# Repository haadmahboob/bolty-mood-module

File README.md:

# Bolty Mood Module

A 40 mm round, 2-layer PCB that gives the Bolty robot a face. An ATtiny85 drives two 3×2 "eyes" made of
12 reverse-mount SK6812MINI-E RGB LEDs, plus a buzzer and a pat button. The main robot sets the mood over
I2C at address `0x42`.

## Specs

| | |
|---|---|
| Board | 40 mm round, 2 layers, 1.6 mm FR-4 |
| MCU | ATtiny85-20SU (SOIC-8 wide), 8 MHz internal |
| LEDs | 12 × SK6812MINI-E, mounted on the back, shining through square holes |
| Sound | CMT-8504 magnetic buzzer, driven by an MMBT3904 |
| Input | 6 × 6 mm tactile button on the face |
| Connector | JST-PH 4-pin: GND, +5V, SCL, SDA |
| Programming | 2 × 3 ISP pads on the back |
| Interface | I2C slave `0x42`, write one byte: 0 idle, 1 happy, 2 sad, 3 angry, 4 sleepy, 5 surprised |

## Folders

| Path | Contents |
|---|---|
| `DESIGN.md` | Design notes: parts, pinout, LED layout |
| `BUILD.md` | Order → solder → program → test guide |
| `JOURNAL.md` | Build journal |
| `kicad/` | KiCad 10 project (schematic, PCB, custom symbol and footprint libraries) |
| `fab/` | Gerbers, drill files, BOM with buy links, positions, assembly PDFs, STEP model |
| `firmware/bolty_mood/` | ATtiny85 test firmware (ATTinyCore) |
| `tools/` | Python scripts that generated the schematic and board and ran the autorouter |
| `reel/` | Progress images and video |

## Status

- [x] Schematic (ERC clean)
- [x] PCB layout and routing (DRC: 0 errors, 0 unconnected, 0 schematic mismatches)
- [x] Fabrication files and BOM
- [ ] PCBs ordered
- [ ] Assembled and tested

## Credits

Designed with help from Claude Code (AI). See `JOURNAL.md` for who did what.

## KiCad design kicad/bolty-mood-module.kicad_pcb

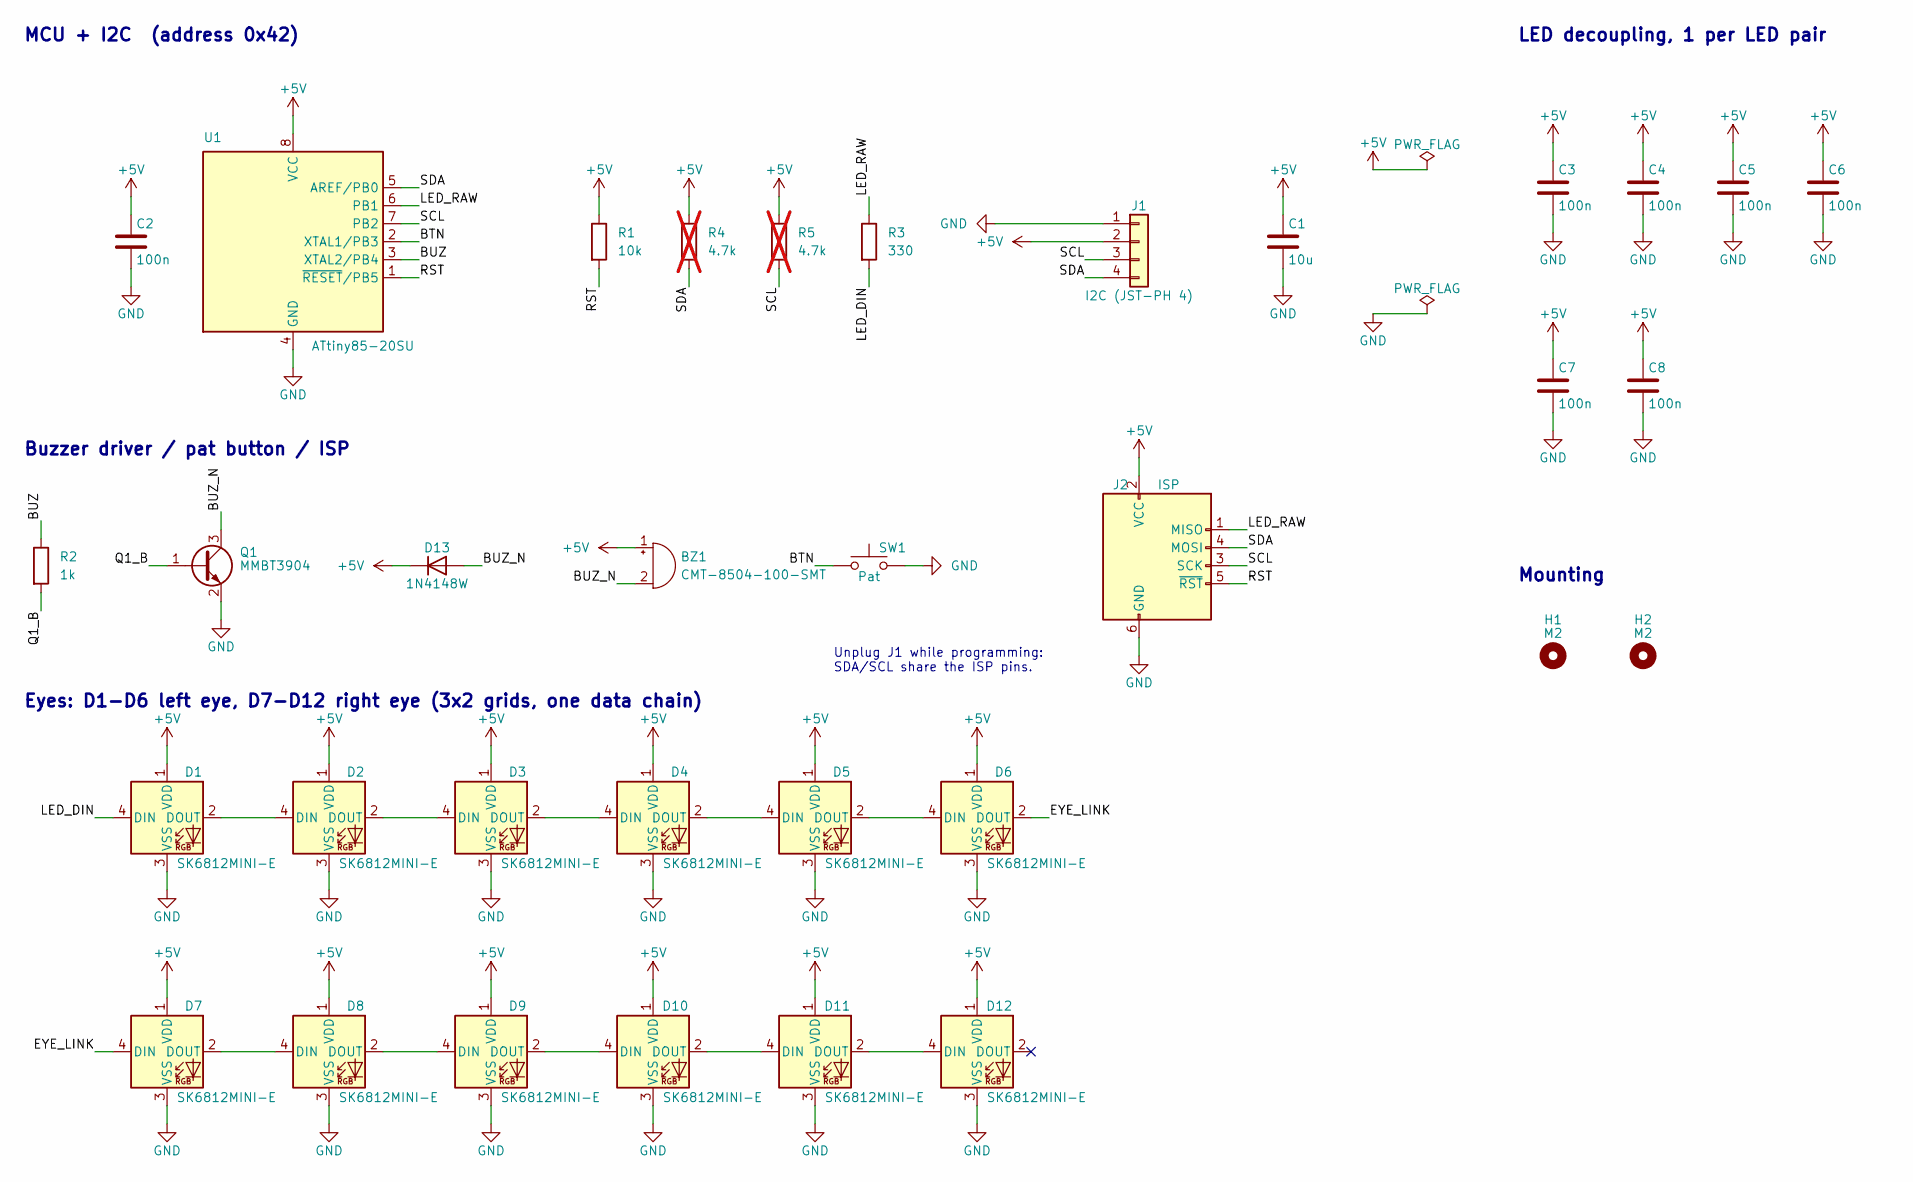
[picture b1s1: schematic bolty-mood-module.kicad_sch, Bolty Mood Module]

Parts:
BZ1: CMT-8504-100-SMT; MagneticBuzzer_CUI_CMT-8504-100-SMT; Part Number CMT-8504-100-SMT-TR
C1: 10u; C_0805_2012Metric; Part Number CL21A106KAYNNNE
C2, C3, C4, C5, C6, C7, C8: 100n; C_0603_1608Metric; Part Number CL10B104KB8NNNC
D1, D2, D3, D4, D5, D6, D7, D8, D9, D10, D11, D12: SK6812MINI-E; LED_SK6812MINI-E_3.2x2.8mm_P1.5mm_ReverseMount; Part Number 4960
D13: 1N4148W; D_SOD-123; Part Number 1N4148W-7-F
H1, H2: M2; MountingHole_2.2mm_M2
J1: I2C (JST-PH 4); JST_PH_B4B-PH-K_1x04_P2.00mm_Vertical; Part Number B4B-PH-K-S(LF)(SN)
J2: ISP; ISP_Pads_2x3_P2.54mm
Q1: MMBT3904; SOT-23; Part Number MMBT3904LT1G
R1: 10k; R_0603_1608Metric; Part Number RC0603FR-0710KL
R2: 1k; R_0603_1608Metric; Part Number RC0603FR-071KL
R3: 330; R_0603_1608Metric; Part Number RC0603FR-07330RL
R4, R5: 4.7k; R_0603_1608Metric; Part Number RC0603FR-074K7L; not fitted
SW1: Pat; SW_SPST_PTS645Sx43SMTR92; Part Number PTS645SM43SMTR92 LFS
U1: ATtiny85-20SU; SOIC-8_5.3x5.3mm_P1.27mm; Part Number ATTINY85-20SU

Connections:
+5V: BZ1.1 (+), C1.1, C2.1, C3.1, C4.1, C5.1, C6.1, C7.1, C8.1, D1.1 (VDD), D2.1 (VDD), D3.1 (VDD), D4.1 (VDD), D5.1 (VDD), D6.1 (VDD), D7.1 (VDD), D8.1 (VDD), D9.1 (VDD), D10.1 (VDD), D11.1 (VDD), D12.1 (VDD), D13.1 (K), J1.2, J2.2 (VCC), R1.1, R4.1, R5.1, U1.8 (VCC)
/BTN: SW1.1, U1.2 (XTAL1/PB3)
/BUZ: R2.1, U1.3 (XTAL2/PB4)
/BUZ_N: BZ1.2 (-), D13.2 (A), Q1.3 (C)
/EYE_LINK: D6.2 (DOUT), D7.4 (DIN)
/LED_DIN: D1.4 (DIN), R3.2
/LED_RAW: J2.1 (MISO), R3.1, U1.6 (PB1)
/Q1_B: Q1.1 (B), R2.2
/RST: J2.5 (~RST), R1.2, U1.1 (~RESET/PB5)
/SCL: J1.3, J2.3 (SCK), R5.2, U1.7 (PB2)
/SDA: J1.4, J2.4 (MOSI), R4.2, U1.5 (AREF/PB0)
GND: C1.2, C2.2, C3.2, C4.2, C5.2, C6.2, C7.2, C8.2, D1.3 (VSS), D2.3 (VSS), D3.3 (VSS), D4.3 (VSS), D5.3 (VSS), D6.3 (VSS), D7.3 (VSS), D8.3 (VSS), D9.3 (VSS), D10.3 (VSS), D11.3 (VSS), D12.3 (VSS), J1.1, J2.6 (GND), Q1.2 (E), SW1.2, U1.4 (GND)
unnamed: D1.2 (DOUT), D2.4 (DIN)
unnamed: D2.2 (DOUT), D3.4 (DIN)
unnamed: D3.2 (DOUT), D4.4 (DIN)
unnamed: D4.2 (DOUT), D5.4 (DIN)
unnamed: D5.2 (DOUT), D6.4 (DIN)
unnamed: D7.2 (DOUT), D8.4 (DIN)
unnamed: D8.2 (DOUT), D9.4 (DIN)
unnamed: D9.2 (DOUT), D10.4 (DIN)
unnamed: D10.2 (DOUT), D11.4 (DIN)
unnamed: D11.2 (DOUT), D12.4 (DIN)

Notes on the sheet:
MCU + I2C (address 0x42)
Buzzer driver / pat button / ISP
Unplug J1 while programming: SDA/SCL share the ISP pins.
Eyes: D1-D6 left eye, D7-D12 right eye (3x2 grids, one data chain)
LED decoupling, 1 per LED pair
Mounting

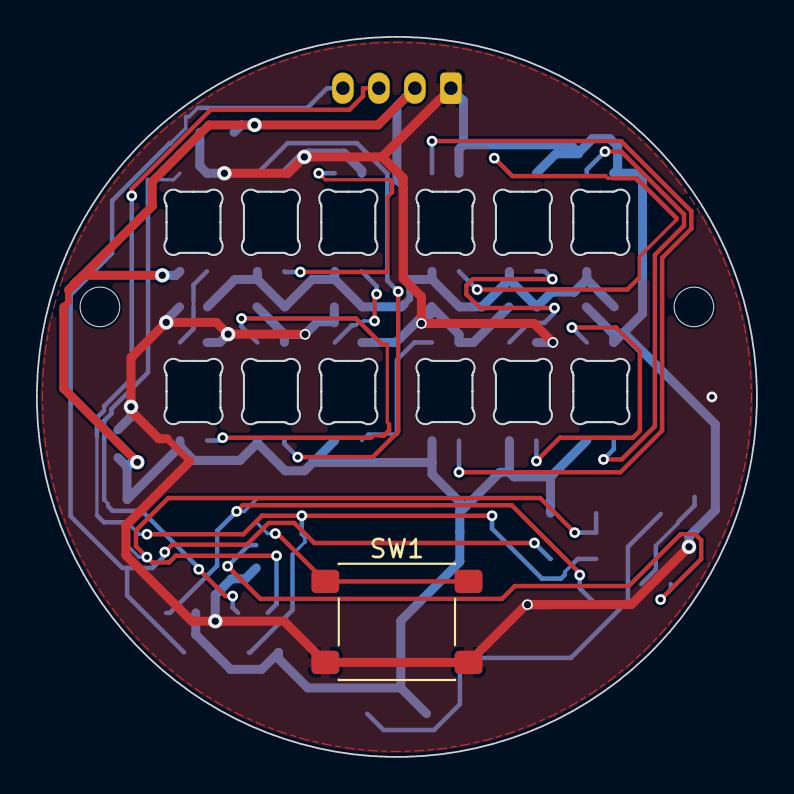
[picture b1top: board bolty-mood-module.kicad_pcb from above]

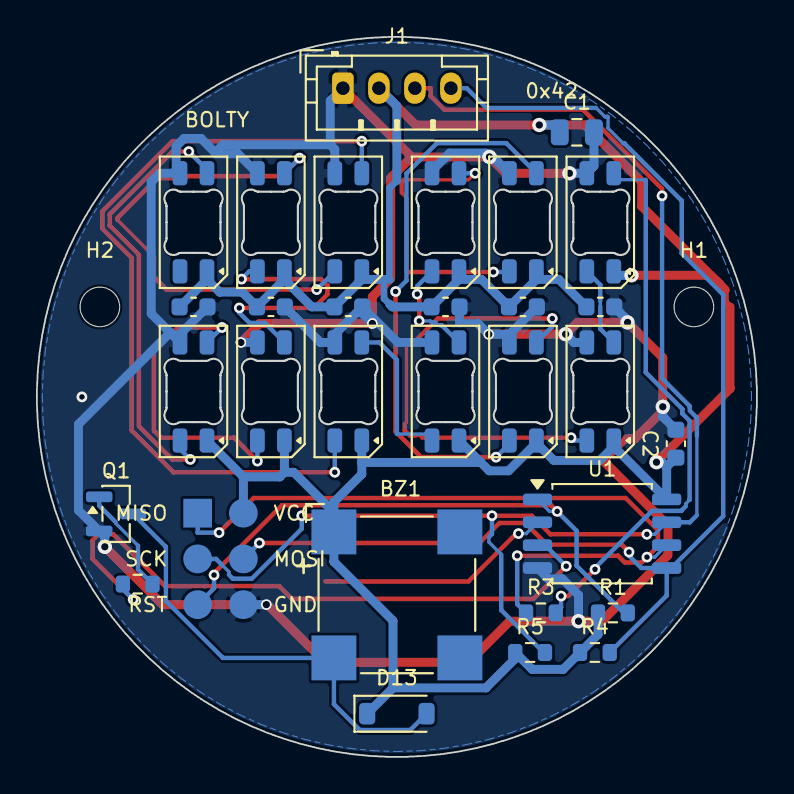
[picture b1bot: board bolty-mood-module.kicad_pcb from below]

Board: 2 copper layers, 40.0 x 40.0 mm, 34 parts (33 on the bottom side), 22 nets.

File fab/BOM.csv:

Reference,Qty per board,Value,Package / Footprint,Manufacturer,MPN,LCSC,Buy link,Notes
U1,1,ATtiny85-20SU,SOIC-8 (5.3 mm wide),Microchip,ATtiny85-20SU,,https://www.digikey.com/en/products/result?keywords=ATtiny85-20SU,Wide-body SOIC (208 mil) - not the narrow SN package
D1-D12,12,SK6812MINI-E,3.2x2.8 mm reverse-mount,Adafruit (OPSCO LEDs),4960,C5149201,https://www.digikey.com/en/products/detail/adafruit-industri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,10-pack of SK6812MINI-E (DigiKey 1528-4960-ND). Mounts on BACK and shines through the board hole
Q1,1,MMBT3904,SOT-23,onsemi,MMBT3904LT1G,,https://www.digikey.com/en/products/result?keywords=MMBT3904LT1G,
D13,1,1N4148W,SOD-123,Diodes Inc.,1N4148W-7-F,,https://www.digikey.com/en/products/result?keywords=1N4148W-7-F,Flyback diode across buzzer. Stripe = cathode = +5V side
BZ1,1,Magnetic buzzer 5 V,8.5x8.5 mm SMD,Same Sky (CUI),CMT-8504-100-SMT-TR,,https://www.digikey.com/en/products/result?keywords=CMT-8504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,Externally driven (passive). Pad 1 +; pads 3/4 are dummy
SW1,1,Tactile switch 6x6,6x6 mm SMD,C&K,PTS645SM43SMTR92 LFS,,https://www.digikey.com/en/products/result?keywords=PTS645SM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,Goes on the FRONT (face)
J1,1,JST-PH 4-pin vertical,THT 2.0 mm,JST,B4B-PH-K-S(LF)(SN),,https://www.digikey.com/en/products/result?keywords=B4B-PH-K-S,Body on BACK; pins soldered from the front
C1,1,10uF 10V+,0805,Samsung,CL21A106KAYNNNE,,https://www.digikey.com/en/products/result?keywords=CL21A106KAYNNNE,Bulk cap next to J1
C2-C8,7,100nF,0603,Samsung,CL10B104KB8NNNC,,https://www.digikey.com/en/products/result?keywords=CL10B104KB8NNNC,C2 = ATtiny; C3-C8 = between each LED pair
R1,1,10k,0603,Yageo,RC0603FR-0710KL,,https://www.digikey.com/en/products/result?keywords=RC0603FR-0710KL,RESET pull-up
R2,1,1k,0603,Yageo,RC0603FR-071KL,,https://www.digikey.com/en/products/result?keywords=RC0603FR-071KL,Q1 base
R3,1,330R,0603,Yageo,RC0603FR-07330RL,,https://www.digikey.com/en/products/result?keywords=RC0603FR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,LED data series resistor
R4-R5,0,4.7k (DNP),0603,Yageo,RC0603FR-074K7L,,https://www.digikey.com/en/products/result?keywords=RC0603FR-074K7L,Do Not Place - fit only if the main robot has no I2C pull-ups
H1-H2,0,M2 hole,2.2 mm NPTH,,,,,Holes in the PCB - no part
PCB,1,40 mm round 2-layer,1.6 mm FR-4,JLCPCB / OSH Park,,,https://jlcpcb.com,Upload fab/bolty-mood-module-gerbers.zip
Cable,1,JST-PH 4-pin cable,2.0 mm,,,,https://www.digikey.com/en/products/result?keywords=JST%20PH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,To the main Bolty controller
Programmer,1,USBasp or Arduino Uno (as ISP),,,,,,Plus a 2x3 2.54 mm pogo-pin clip OR 6 hand-held pogo pins; or solder 6 thin wires temporarily

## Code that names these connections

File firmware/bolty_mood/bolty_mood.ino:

// Bolty Mood Module firmware — first bring-up + test version.
// Board: ATtiny85 @ 8 MHz internal (ATTinyCore: "ATtiny25/45/85 (No bootloader)",
//        Clock "8 MHz (internal)", LTO enabled). Burn Bootloader once to set fuses.
// Program over the 2x3 ISP pads with a USBasp or "Arduino as ISP". Unplug J1 first.
//
// Pins (ATTinyCore numbering = PBx):
//   PB0 SDA, PB2 SCL  -> I2C slave at 0x42
//   PB1 LED data      -> D1..D12 SK6812MINI-E chain (through R3 330R)
//   PB3 button (SW1)  -> to GND, internal pull-up
//   PB4 buzzer        -> Q1 base through R2 1k
//
// On power-up it runs a self-test: beep, then lights every LED in chain order
// (D1..D12) red, green, blue. If the walk stops at some LED, check that LED and the
// one before it (DOUT -> DIN).
//
// I2C protocol: master writes one byte: 0 idle, 1 happy, 2 sad, 3 angry, 4 sleepy, 5 surprised.
// No I2C byte for 3 s -> idle blink. Button press -> happy + chirp.

#include <tinyNeoPixel.h>
#include <Wire.h>

#define PIN_LED  PIN_PB1
#define PIN_BTN  PIN_PB3
#define PIN_BUZ  PIN_PB4
#define NUM_LEDS 12
#define I2C_ADDR 0x42
#define BRIGHTNESS 64   // ~25 %: 12 LEDs at full white would draw ~600 mA

tinyNeoPixel strip(NUM_LEDS, PIN_LED, NEO_GRB + NEO_KHZ800);

// Grid as seen from the FRONT: 6 columns (0-2 left eye, 3-5 right eye) x 2 rows (0 top).
// The data chain snakes up/down the columns, so map (col,row) -> chain index.
const uint8_t LED_AT[6][2] = {
  {0, 1}, {3, 2}, {4, 5},     // left eye:  D1/D2, D4/D3, D5/D6
  {7, 6}, {8, 9}, {11, 10},   // right eye: D8/D7, D9/D10, D12/D11
};

enum Mood : uint8_t { IDLE, HAPPY, SAD, ANGRY, SLEEPY, SURPRISED, MOOD_COUNT };

// Per mood: which of the 3x2 cells light in ONE eye (bit = col*2 + row), mirrored to the other eye.
//   bit layout:  col0 col1 col2
//        top      0    2    4
//        bottom   1    3    5
const uint8_t MOOD_SHAPE[MOOD_COUNT] = {
  0b111111,  // IDLE: full eye
  0b100101,  // HAPPY: ^ shape (outer bottoms, middle top)
  0b010010,  // SAD: middle bottom + outer tops... drooping
  0b011001,  // ANGRY: slanted
  0b101010,  // SLEEPY: bottom row only
  0b111111,  // SURPRISED: full, bright
};
const uint32_t MOOD_COLOR[MOOD_COUNT] = {
  0x0040FF,  // idle blue
  0x00FF40,  // happy green
  0x2020FF,  // sad dim blue
  0xFF0000,  // angry red
  0x804000,  // sleepy amber
  0xFFFFFF,  // surprised white
};

volatile uint8_t pendingMood = 0xFF;
volatile uint32_t lastI2cMs = 0;
uint8_t mood = IDLE;

void onReceive(int count) {
  while (Wire.available()) {
    uint8_t b = Wire.read();
    if (b < MOOD_COUNT) pendingMood = b;
  }
  lastI2cMs = millis();
}

void showMood(uint8_t m, bool on = true) {
  strip.clear();
  if (on) {
    for (uint8_t col = 0; col < 6; col++) {
      uint8_t c = (col < 3) ? col : (5 - col);   // mirror right eye
      for (uint8_t row = 0; row < 2; row++) {
        if (MOOD_SHAPE[m] & (1 << (c * 2 + row))) {
          strip.setPixelColor(LED_AT[col][row], MOOD_COLOR[m]);
        }
      }
    }
  }
  strip.show();
}

void chirp() {
  tone(PIN_BUZ, 2000, 60);
  delay(80);
  tone(PIN_BUZ, 3000, 60);
}

void selfTest() {
  tone(PIN_BUZ, 4000, 150);   // CMT-8504 is loudest near 4 kHz
  delay(200);
  const uint32_t colors[3] = {0xFF0000, 0x00FF00, 0x0000FF};
  for (uint8_t c = 0; c < 3; c++) {
    for (uint8_t i = 0; i < NUM_LEDS; i++) {
      strip.clear();
      strip.setPixelColor(i, colors[c]);
      strip.show();
      delay(120);
    }
  }
  strip.clear();
  strip.show();
}

void setup() {
  pinMode(PIN_BTN, INPUT_PULLUP);
  pinMode(PIN_BUZ, OUTPUT);
  digitalWrite(PIN_BUZ, LOW);
  strip.begin();
  strip.setBrightness(BRIGHTNESS);
  selfTest();

  Wire.begin(I2C_ADDR);
  Wire.onReceive(onReceive);
  lastI2cMs = millis();
  showMood(IDLE);
}

void loop() {
  static bool lastBtn = HIGH;
  static uint32_t blinkMs = 0;

  if (pendingMood != 0xFF) {
    noInterrupts();
    mood = pendingMood;
    pendingMood = 0xFF;
    interrupts();
    showMood(mood);
  }

  bool btn = digitalRead(PIN_BTN);
  if (lastBtn == HIGH && btn == LOW) {   // pressed
    mood = HAPPY;
    showMood(mood);
    chirp();
  }
  lastBtn = btn;

  // idle blink when the robot hasn't talked for 3 s
  uint32_t now = millis();
  noInterrupts();
  uint32_t quiet = now - lastI2cMs;
  interrupts();
  if (quiet > 3000 && mood == IDLE) {
    if (now - blinkMs > 3000) {          // blink every 3 s
      showMood(IDLE, false);
      delay(150);
      showMood(IDLE, true);
      blinkMs = now;
    }
  }
  delay(10);
}
